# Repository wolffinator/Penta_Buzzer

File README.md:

# Penta Buzzer
A buzz for the fingers.  
Open source code and assembly for a mobile 4 buzzer hand thingy.  
Purpose of this device is to provide a pre-programmed buzzing pattern to each of the 4 fingers.  
## 💡 Current Features
* Runs program to buzz each finger at set intervals.
* Battery life of over 4hrs while running.
* On/Off button.
* Charge port that also doubles as programming port.
## ⚠️ Word of Warning
* This project is at its infancy. The current hardware design will change and may not work with future versions of this code.
* Project requires intermediate skills in soldering. There are a few surface mount soldering points and many close solder pads. Practice technique if you are unsure.
* ESP32 does not have reverse polarity protection (ask me how I know). Check your work before you fry your board.
* This is not a well designed product (yet). Parts will and have failed. 
### BOM
* [Seeed Studio XIAO ESP32-C3][esp32_c3_link]. This is the microcontroller used in this project. This was chosen due to its built in connectivity and battery management circuitry.  
* [DRV 8833][drv_8833_link]. This is the motor controller which will power each of the 4 buzzers.  
* [MakerFocus 2A 5V Charging Protection Module][makerfocus_charge_discharge_module_link]. This is used to provide 5v for the motors and show current battery capacity. The charging of the battery is accomplished by the microcontroller circuit.
* [9 by 20 by 30mm lithium ion battery][lithium_ion_battery_link] 
* Heat Shrink
* 30AWG stranded wire.
* 22AWG solid core wire.
### 3d Printable Case

There is an OpenScad document in the Models directory that can be 3d printed as an enclosure for the whole setup. I plan to rework this as it was a pain to assemble.
## 🛠 Flash Firmware (For Users)

## 🛠 Installation Setup (For Developers)
### Install Arduino IDE
### Install Board Support Packages for ESP32
### Install Visual Studio Code (VS-Code)

### Install Platform IO Extension for VS-Code

### Flash Board Firmware

## 🔬 Future plans
### Version 2
* Goal of Version 2 is to see if I can create a PCB that works, is small, and combines many boards into a small footprint.
* Explore fabrication proccess
* Additional goal is for me (wolffinator) to get better at SMD soldering since this will most likely require some rework/repair.
### Version 2 Progress:
#### Schematic

#### PCB Layout

### Version 3
* Goal of Version 3 is to make the design as easy to produce as possible.
* I would love to provide a link for users here to click on and get a quote from one or (or many) PCB manufacturers and have them solder all of the components. It looks like Version 2 requires some hand soldering of SMD components afterwards, which can be difficult.
* Provide a link to a 3d printed case.
* Simplify case assembly and wire soldering as much as possible.
* Include more detailed assembly instructions.

[drv_8833_link]: https://www.amazon.com/gp/product/B0BGLH27GG/ref=sw_img_1?smid=A2QD586WPO9XSR&psc=1
[esp32_c3_link]: https://www.digikey.com/en/products/detail/seeed-technology-co-ltd/113991054/16652880?s=N4IgTCBcDaIM4FMkBMAEcAuBXZBLA9qgBoCSAggPKoCiAygAoDMYAwoyALoC%2BQA
[makerfocus_charge_discharge_module_link]: https://www.amazon.com/gp/product/B07PZT3ZW2/ref=ppx_yo_dt_b_search_asin_image?ie=UTF8&psc=1
[lithium_ion_battery_link]: https://www.aliexpress.us/item/3256804370986754.html?spm=a2g0o.order_list.order_list_main.4.64bc18023Wexc3&gatewayAdapt=glo2usa

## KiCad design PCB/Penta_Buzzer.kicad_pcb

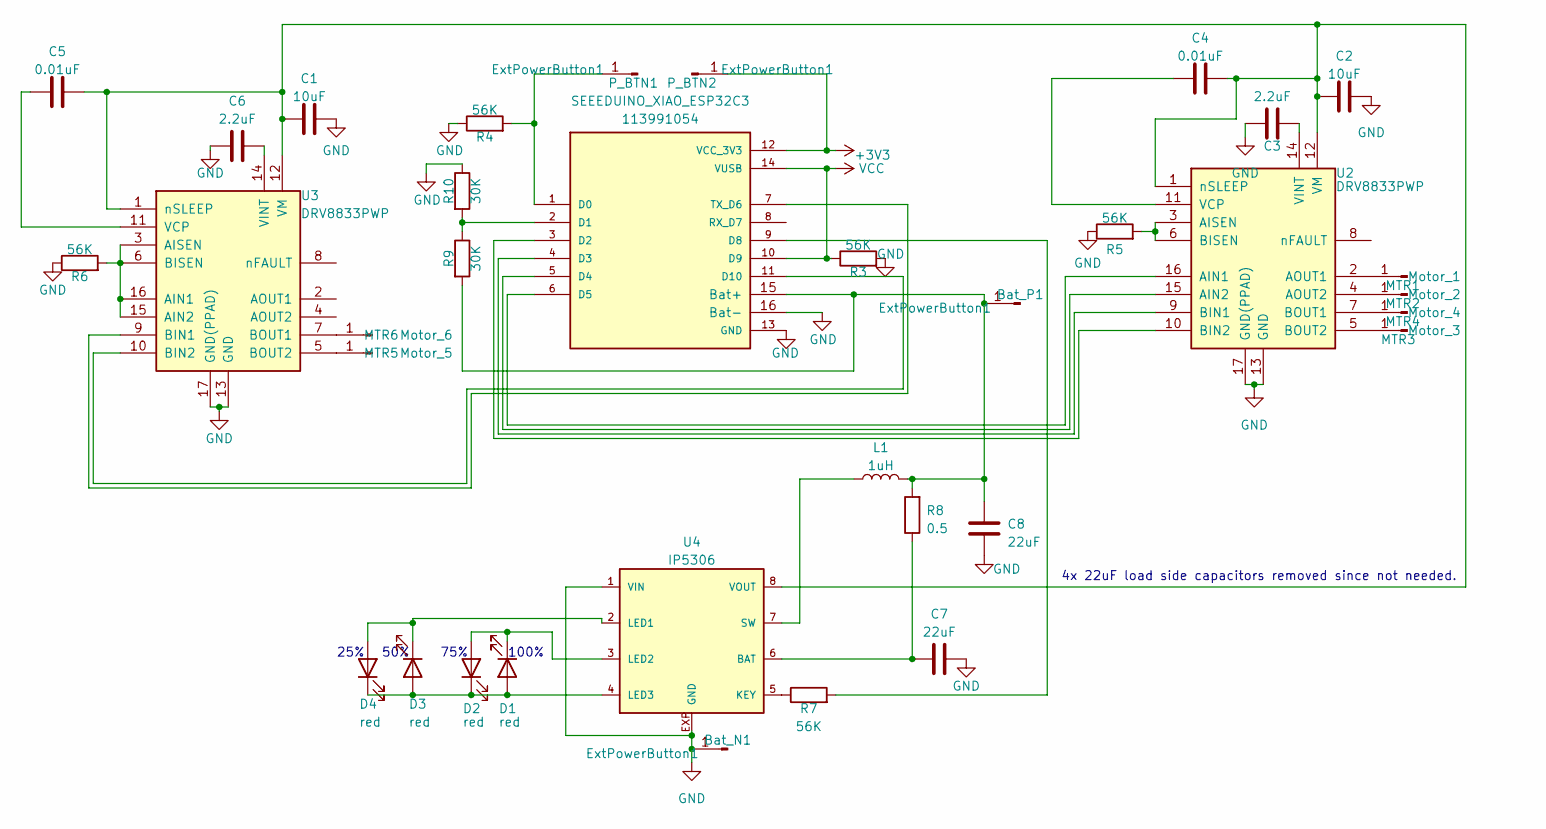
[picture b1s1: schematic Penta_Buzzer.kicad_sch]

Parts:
Bat_N1: ExtPowerButton1; Pin_D1.0mm_L10.0mm
Bat_P1: ExtPowerButton1; Pin_D1.0mm_L10.0mm
C1, C2: 10uF; C_1206_3216Metric_Pad1.33x1.80mm_HandSolder
C3, C6: 2.2uF; C_1206_3216Metric_Pad1.33x1.80mm_HandSolder
C4, C5: 0.01uF; C_1206_3216Metric_Pad1.33x1.80mm_HandSolder
C7, C8: 22uF; C_1206_3216Metric_Pad1.33x1.80mm_HandSolder
D1, D2, D3, D4: red; LED_0805_2012Metric_Pad1.15x1.40mm_HandSolder
L1: 1uH; L_1206_3216Metric_Pad1.42x1.75mm_HandSolder
MTR1: Motor_1; Pin_D1.0mm_L10.0mm
MTR2: Motor_2; Pin_D1.0mm_L10.0mm
MTR3: Motor_3; Pin_D1.0mm_L10.0mm
MTR4: Motor_4; Pin_D1.0mm_L10.0mm
MTR5: Motor_5; Pin_D1.0mm_L10.0mm
MTR6: Motor_6; Pin_D1.0mm_L10.0mm
P_BTN1, P_BTN2: ExtPowerButton1; Pin_D1.0mm_L10.0mm
R3, R4, R5, R6, R7: 56K; R_1206_3216Metric_Pad1.30x1.75mm_HandSolder
R8: 0.5; R_1206_3216Metric_Pad1.30x1.75mm_HandSolder
R9, R10: 30K; R_1206_3216Metric_Pad1.30x1.75mm_HandSolder
SEEEDUINO_XIAO_ESP32C3: 113991054; MODULE_113991054; PARTREV 23/05/2022
U2, U3: DRV8833PWP; HTSSOP-16-1EP_4.4x5mm_P0.65mm_EP3.4x5mm_Mask2.46x2.31mm_The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
U4: IP5306; SOP8-P

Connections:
+3V3: P_BTN2.1, SEEEDUINO_XIAO_ESP32C3.12 (VCC_3V3)
GND: Bat_N1.1, C1.2, C2.2, C3.2, C6.2, C7.2, C8.1, R3.2, R4.1, R5.1, R6.1, R10.1, SEEEDUINO_XIAO_ESP32C3.13 (GND), SEEEDUINO_XIAO_ESP32C3.16 (Bat-), U2.13 (GND), U2.17 (GND(PPAD)), U3.13 (GND), U3.17 (GND(PPAD)), U4.1 (VIN), U4.EXP (GND)
unnamed: Bat_P1.1, C8.2, L1.2, R8.2, R9.2, SEEEDUINO_XIAO_ESP32C3.15 (Bat+)
unnamed: D1.2 (A), D2.1 (K), D3.2 (A), D4.1 (K), U4.4 (LED3)
unnamed: D1.1 (K), D2.2 (A), U4.3 (LED2)
unnamed: D3.1 (K), D4.2 (A), U4.2 (LED1)
unnamed: MTR1.1, U2.2 (AOUT1)
unnamed: MTR2.1, U2.4 (AOUT2)
unnamed: MTR3.1, U2.5 (BOUT2)
unnamed: MTR4.1, U2.7 (BOUT1)
unnamed: MTR5.1, U3.5 (BOUT2)
unnamed: MTR6.1, U3.7 (BOUT1)
unnamed: P_BTN1.1, R4.2, SEEEDUINO_XIAO_ESP32C3.1 (D0)
unnamed: R9.1, R10.2, SEEEDUINO_XIAO_ESP32C3.2 (D1)
unnamed: SEEEDUINO_XIAO_ESP32C3.3 (D2), U2.10 (BIN2)
unnamed: SEEEDUINO_XIAO_ESP32C3.4 (D3), U2.9 (BIN1)
unnamed: SEEEDUINO_XIAO_ESP32C3.5 (D4), U2.15 (AIN2)
unnamed: SEEEDUINO_XIAO_ESP32C3.6 (D5), U2.16 (AIN1)
unnamed: R7.2, SEEEDUINO_XIAO_ESP32C3.9 (D8)
unnamed: SEEEDUINO_XIAO_ESP32C3.11 (D10), U3.10 (BIN2)
unnamed: SEEEDUINO_XIAO_ESP32C3.7 (TX_D6), U3.9 (BIN1)
unnamed: R5.2, U2.3 (AISEN), U2.6 (BISEN)
unnamed: C4.1, U2.11 (VCP)
unnamed: C3.1, U2.14 (VINT)
unnamed: C1.1, C2.1, C4.2, C5.2, U2.1 (nSLEEP), U2.12 (VM), U3.1 (nSLEEP), U3.12 (VM), U4.8 (VOUT)
unnamed: R6.2, U3.3 (AISEN), U3.6 (BISEN), U3.15 (AIN2), U3.16 (AIN1)
unnamed: C5.1, U3.11 (VCP)
unnamed: C6.1, U3.14 (VINT)
unnamed: C7.1, R8.1, U4.6 (BAT)
unnamed: R7.1, U4.5 (KEY)
unnamed: L1.1, U4.7 (SW)
VCC: R3.1, SEEEDUINO_XIAO_ESP32C3.10 (D9), SEEEDUINO_XIAO_ESP32C3.14 (VUSB)

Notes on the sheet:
75%
100%
4x 22uF load side capacitors removed since not needed.
25%
50%

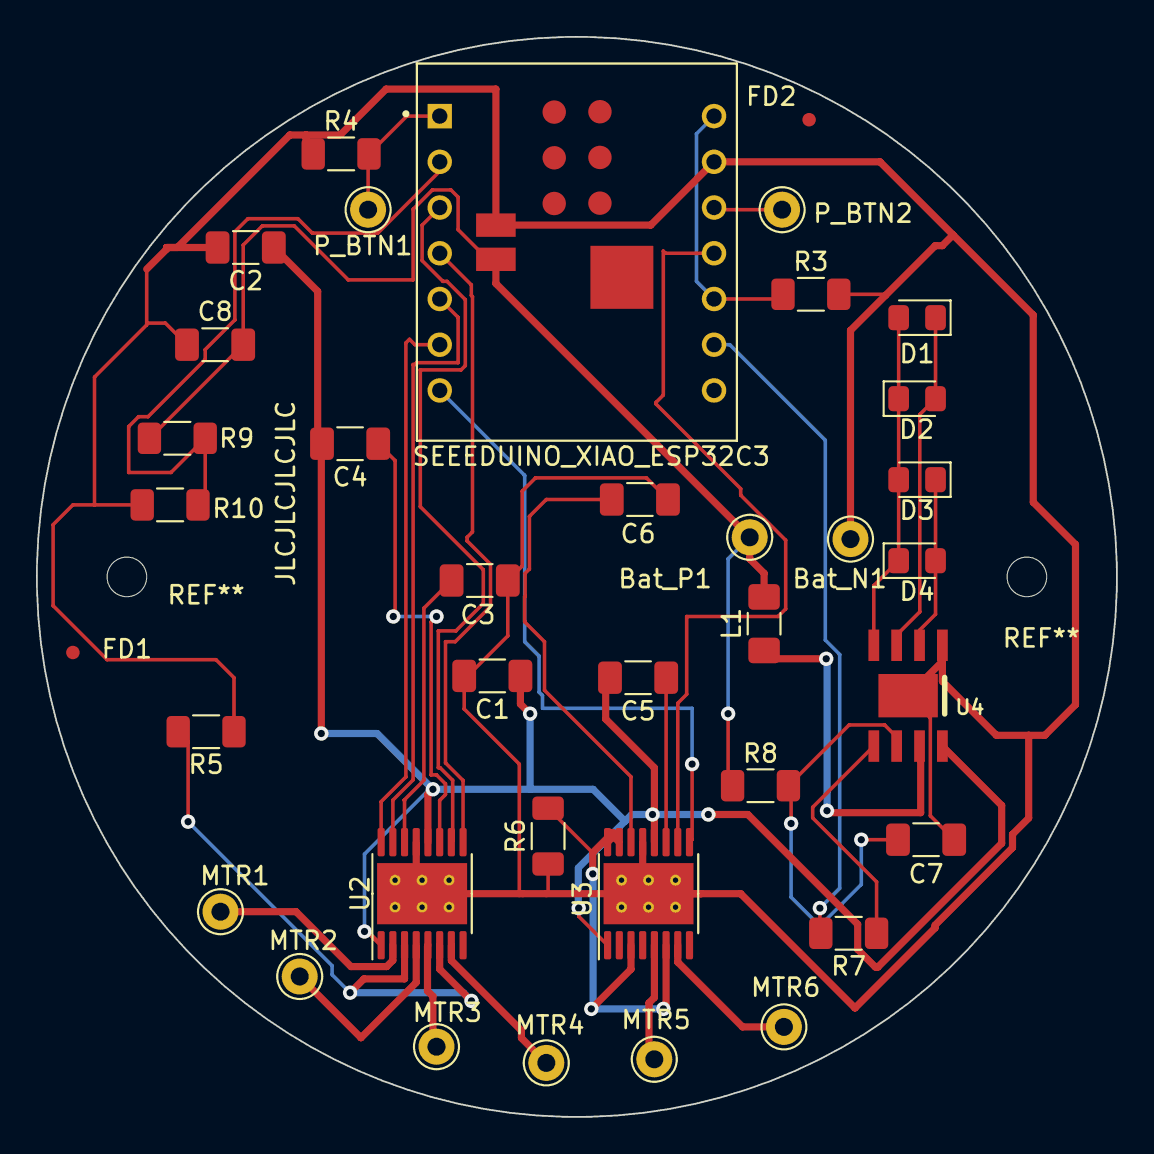
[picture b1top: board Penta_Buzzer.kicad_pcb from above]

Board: 2 copper layers, 60.0 x 60.0 mm, 37 parts (0 on the bottom side), 32 nets.

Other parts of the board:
FD1, FD2: Fiducial_0.75mm_Mask1.5mm

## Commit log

2023-06-10 Updating Gitignore for PlatformIO
2023-06-11 Adding mk1 model and more documentation
2023-06-11 More documentation
2023-06-17 Schematic for V2 first commit
2023-06-17 Added missing library
2023-06-21 Gitignore
2023-06-21 Gitignore and more updates to schematic
2023-06-21 More readme updates
2024-01-01 Current version I have for my Father
2024-01-02 Updating PCB for new pulldown resistors, sleep for motor drivers, and new pinnout for wakup by GPIO.
2024-01-02 More progress. This is the current code my Father has.
